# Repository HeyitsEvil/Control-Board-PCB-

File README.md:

# Control-Board-PCB-
This is an iteration following one of the pcb design project in the team
As the library is made by the team, i will not release any code related content related the board

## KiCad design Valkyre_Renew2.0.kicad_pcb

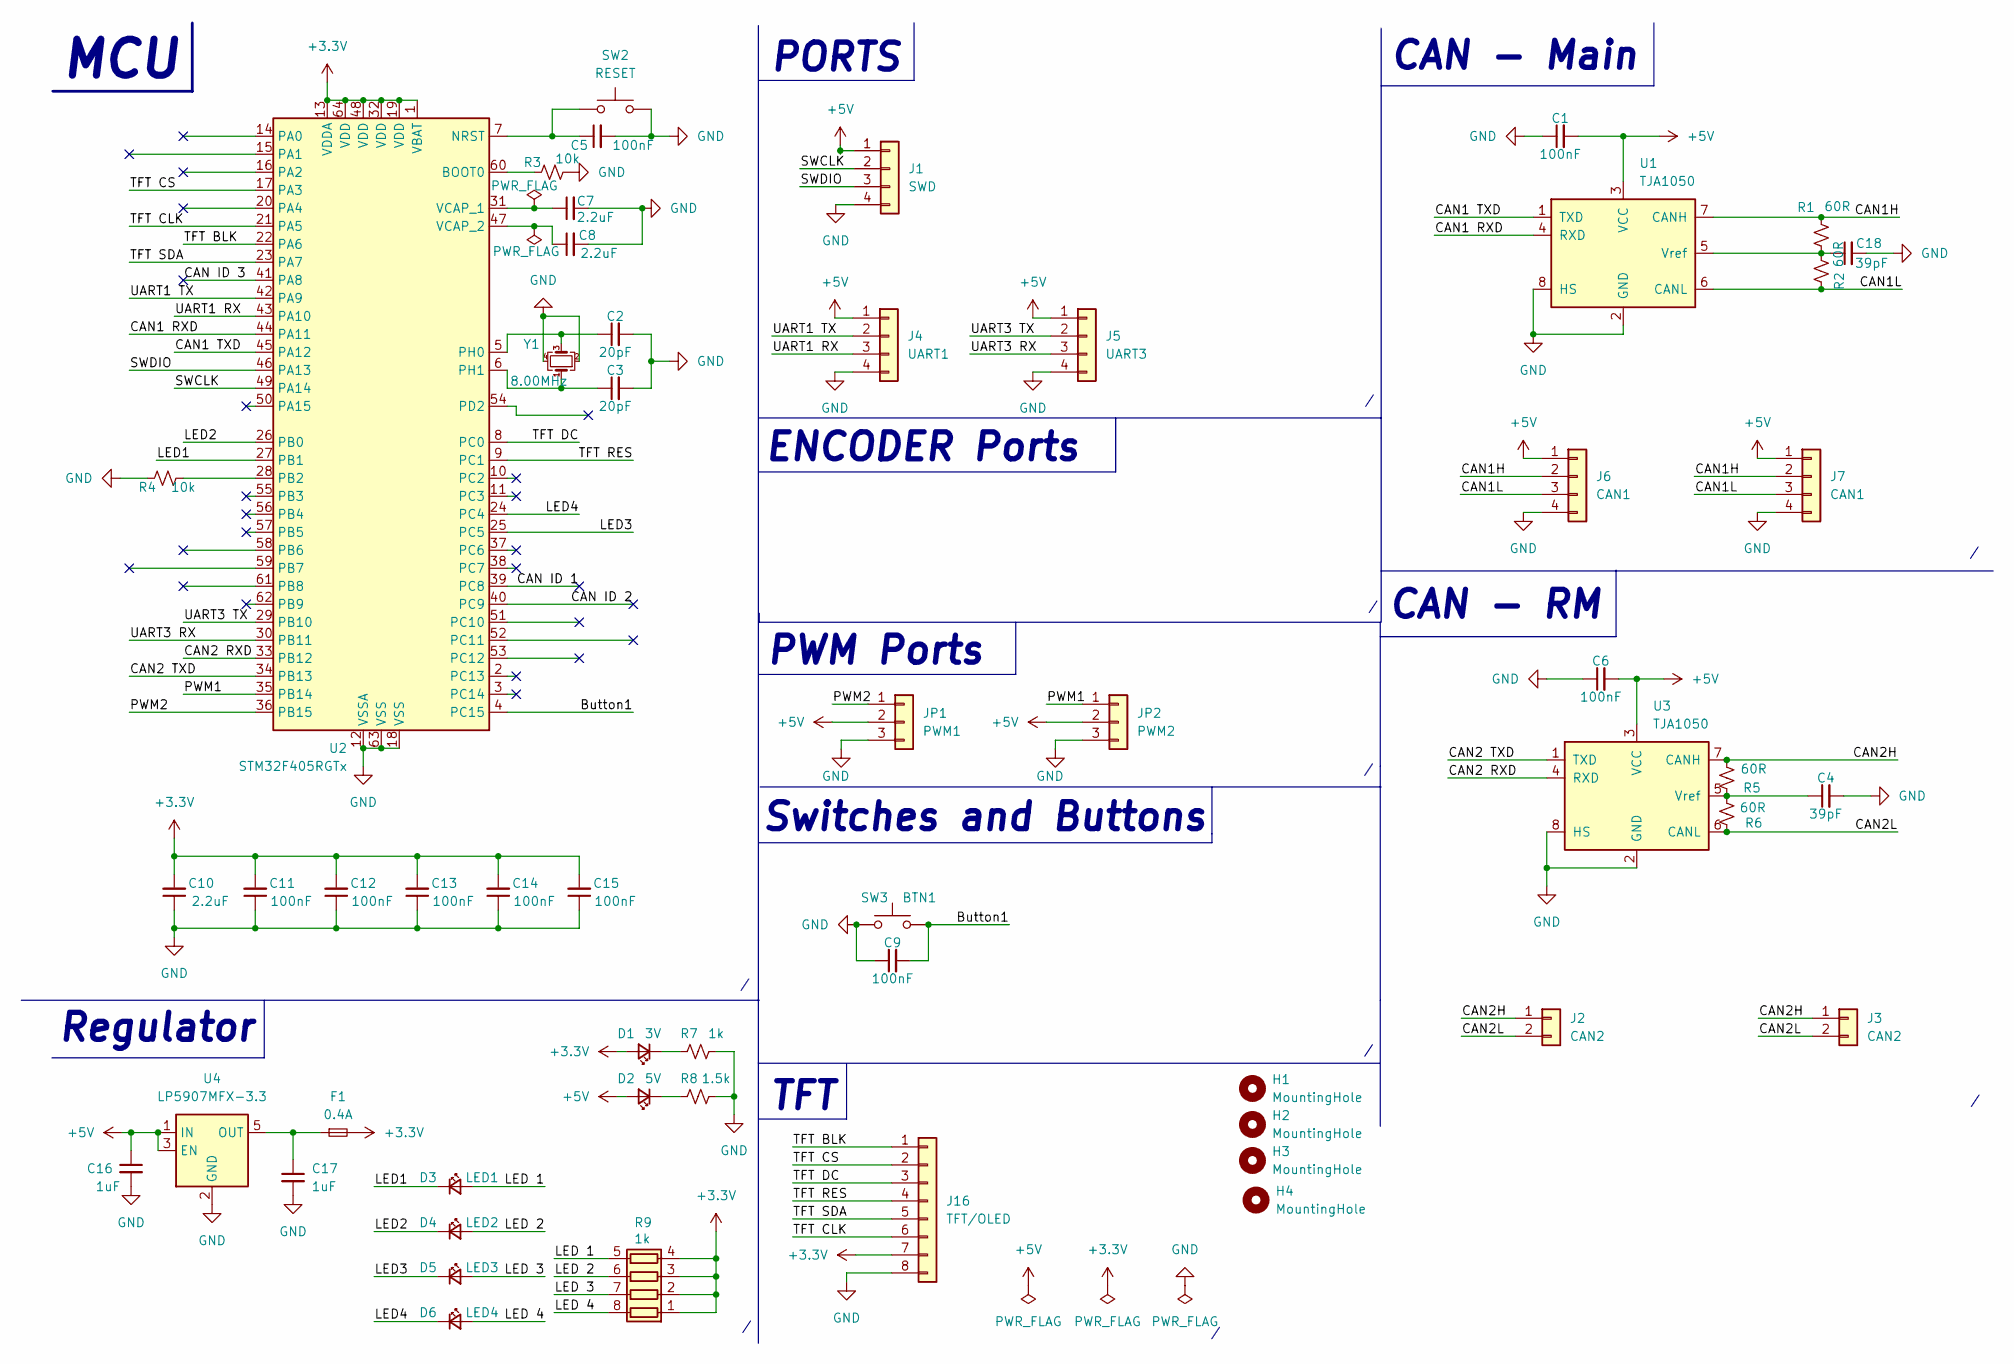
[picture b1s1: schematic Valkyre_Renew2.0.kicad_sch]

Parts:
C1, C5, C6, C9, C11, C12, C13, C14, C15: 100nF; C_0603_1608Metric
C2, C3: 20pF; C_0603_1608Metric
C4, C18: 39pF; C_0603_1608Metric
C7, C8, C10: 2.2uF; C_0603_1608Metric
C16, C17: 1uF; C_0603_1608Metric
D1: 3V; LED_0603_1608Metric
D2: 5V; LED_0603_1608Metric
D3: LED1; LED_0603_1608Metric
D4: LED2; LED_0603_1608Metric
D5: LED3; LED_0603_1608Metric
D6: LED4; LED_0603_1608Metric
F1: 0.4A; R_0603_1608Metric
H1, H2, H3, H4: MountingHole; MountingHole_3.2mm_M3
J1: SWD; JST_XH_B4B-XH-A_1x04_P2.50mm_Vertical
J2, J3: CAN2; JST_XH_B2B-XH-A_1x02_P2.50mm_Vertical
J4: UART1; JST_XH_B4B-XH-A_1x04_P2.50mm_Vertical
J5: UART3; JST_XH_B4B-XH-A_1x04_P2.50mm_Vertical
J6, J7: CAN1; JST_XH_B4B-XH-A_1x04_P2.50mm_Vertical
J16: TFT/OLED; PinSocket_1x08_P2.54mm_Vertical
JP1: PWM1; JST_XH_B3B-XH-A_1x03_P2.50mm_Vertical
JP2: PWM2; JST_XH_B3B-XH-A_1x03_P2.50mm_Vertical
R1, R2, R5, R6: 60R; R_0603_1608Metric
R3, R4: 10k; R_0603_1608Metric
R7: 1k; R_0603_1608Metric
R8: 1.5k; R_0603_1608Metric
R9: 1k; R_Array_Convex_4x0603
SW2: RESET; SW_Push
SW3: BTN1; SW_Push
U1, U3: TJA1050; SOIC-8_3.9x4.9mm_P1.27mm
U2: STM32F405RGTx; LQFP-64_10x10mm_P0.5mm
U4: LP5907MFX-3.3; SOT-23-5
Y1: 8.00MHz; Crystal_SMD_3225-4Pin_3.2x2.5mm

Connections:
+3.3V: C10.2, C11.2, C12.2, C13.2, C14.2, C15.2, D1.2 (A), F1.2, J16.7, R9.1 (R1.1), R9.2 (R2.1), R9.3 (R3.1), R9.4 (R4.1), U2.1 (VBAT), U2.13 (VDDA), U2.19 (VDD), U2.32 (VDD), U2.48 (VDD), U2.64 (VDD)
+5V: C1.2, C6.2, C16.1, D2.2 (A), J1.1, J4.1, J5.1, J6.1, J7.1, JP1.2, JP2.2, U1.3 (VCC), U3.3 (VCC), U4.1 (IN), U4.3 (EN)
/Button1: C9.2, SW3.2, U2.4 (PC15)
/CAN1 RXD: U1.4 (RXD), U2.44 (PA11)
/CAN1 TXD: U1.1 (TXD), U2.45 (PA12)
/CAN1H: J6.2, J7.2, R1.2, U1.7 (CANH)
/CAN1L: J6.3, J7.3, R2.2, U1.6 (CANL)
/CAN2 RXD: U2.33 (PB12), U3.4 (RXD)
/CAN2 TXD: U2.34 (PB13), U3.1 (TXD)
/CAN2H: J2.1, J3.1, R5.2, U3.7 (CANH)
/CAN2L: J2.2, J3.2, R6.1, U3.6 (CANL)
/CAN ID 1: U2.39 (PC8)
/CAN ID 2: U2.40 (PC9)
/CAN ID 3: U2.41 (PA8)
/LED1: D3.1 (K), U2.27 (PB1)
/LED2: D4.1 (K), U2.26 (PB0)
/LED3: D5.1 (K), U2.25 (PC5)
/LED4: D6.1 (K), U2.24 (PC4)
/LED 1: D3.2 (A), R9.5 (R4.2)
/LED 2: D4.2 (A), R9.6 (R3.2)
/LED 3: D5.2 (A), R9.7 (R2.2)
/LED 4: D6.2 (A), R9.8 (R1.2)
/PWM1: JP2.1, U2.35 (PB14)
/PWM2: JP1.1, U2.36 (PB15)
/SWCLK: J1.2, U2.49 (PA14)
/SWDIO: J1.3, U2.46 (PA13)
/TFT BLK: J16.1, U2.22 (PA6)
/TFT CLK: J16.6, U2.21 (PA5)
/TFT CS: J16.2, U2.17 (PA3)
/TFT DC: J16.3, U2.8 (PC0)
/TFT RES: J16.4, U2.9 (PC1)
/TFT SDA: J16.5, U2.23 (PA7)
/UART1 RX: J4.3, U2.43 (PA10)
/UART1 TX: J4.2, U2.42 (PA9)
/UART3 RX: J5.3, U2.30 (PB11)
/UART3 TX: J5.2, U2.29 (PB10)
GND: C1.1, C2.2, C3.2, C4.2, C5.2, C6.1, C7.2, C8.2, C9.1, C10.1, C11.1, C12.1, C13.1, C14.1, C15.1, C16.2, C17.2, C18.2, J1.4, J4.4, J5.4, J6.4, J7.4, J16.8, JP1.3, JP2.3, R3.2, R4.1, R7.1, R8.1, SW2.2, SW3.1, U1.2 (GND), U1.8 (HS), U2.12 (VSSA), U2.18 (VSS), U2.63 (VSS), U3.2 (GND), U3.8 (HS), U4.2 (GND), Y1.2, Y1.4
unnamed: D1.1 (K), R7.2
unnamed: D2.1 (K), R8.2
unnamed: C18.1, R1.1, R2.1, U1.5 (Vref)
unnamed: R3.1, U2.60 (BOOT0)
unnamed: C5.1, SW2.1, U2.7 (NRST)
unnamed: R4.2, U2.28 (PB2)
unnamed: C2.1, U2.5 (PH0), Y1.3
unnamed: C3.1, U2.6 (PH1), Y1.1
unnamed: C7.1, U2.31 (VCAP_1)
unnamed: C8.1, U2.47 (VCAP_2)
unnamed: C4.1, R5.1, R6.2, U3.5 (Vref)
unnamed: C17.1, F1.1, U4.5 (OUT)

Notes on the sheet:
Regulator
PWM Ports
ENCODER Ports
CAN - Main
MCU
Switches and Buttons
CAN - RM
TFT
PORTS

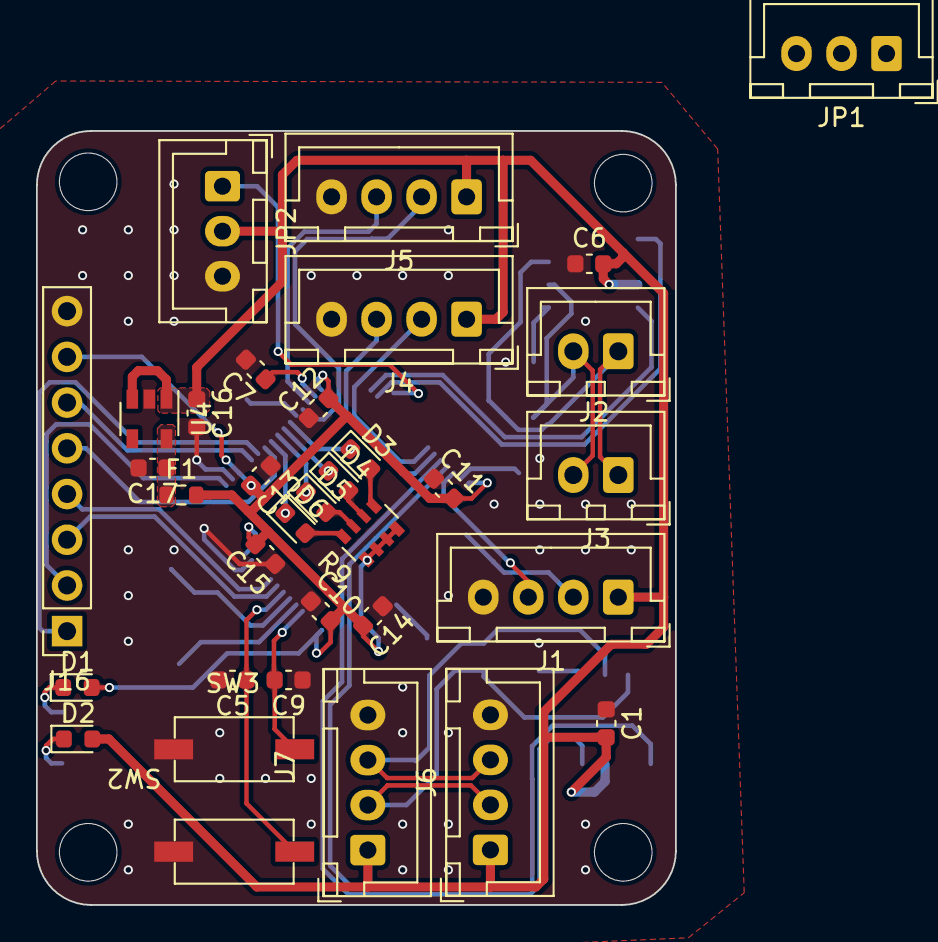
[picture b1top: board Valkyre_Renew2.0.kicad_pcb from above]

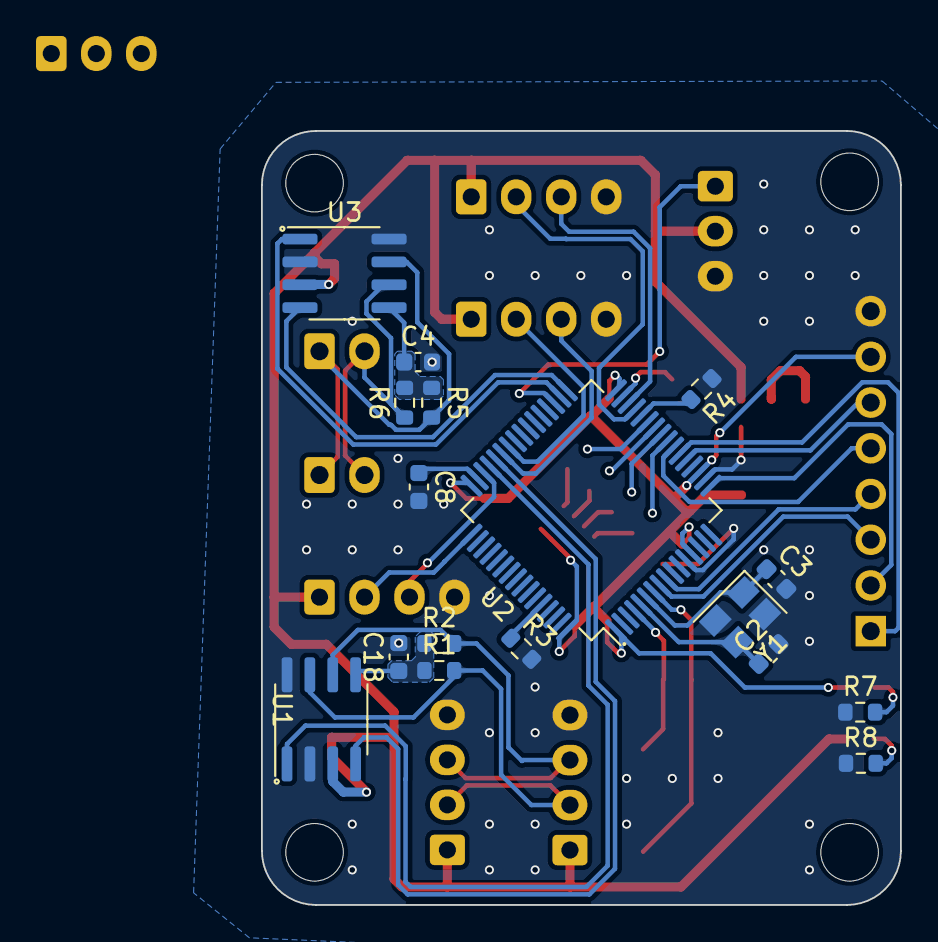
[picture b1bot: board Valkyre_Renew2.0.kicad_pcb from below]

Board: 2 copper layers, 35.5 x 43.0 mm, 55 parts (17 on the bottom side), 46 nets.
